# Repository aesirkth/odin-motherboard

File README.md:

# ÆSIR - Odin Motherboard
Odin Motherboard KiCad Design Files

This repository contains the motherboard KiCad design files for the ÆSIR Odin hybrid rocket.
Its main purpose is to house the on-board computer, a Teensy v3.6, and the breakouts to all external components in the rocket. These include: GPS, Go Pro, telemetry, servo, video/camera transmission, accelerometer, umbilical cord, and a safety pin. Use the reference_breakout.txt file to see where each output goes to. 

aesir.lib contains the schematic symbols for the BMP180, MPU-9250, and the motherboard plate (68 mm diameter)

AESIR.pretty contains the footprints for the BMP180, MPU-9250, and the motherboard plate (68 mm diameter).

The Teensy v3.6 KiCad component is required.
Download the schematic symbols and footprints from: 
https://github.com/XenGi/teensy_library

Watch our progress at http://aesir.se/!

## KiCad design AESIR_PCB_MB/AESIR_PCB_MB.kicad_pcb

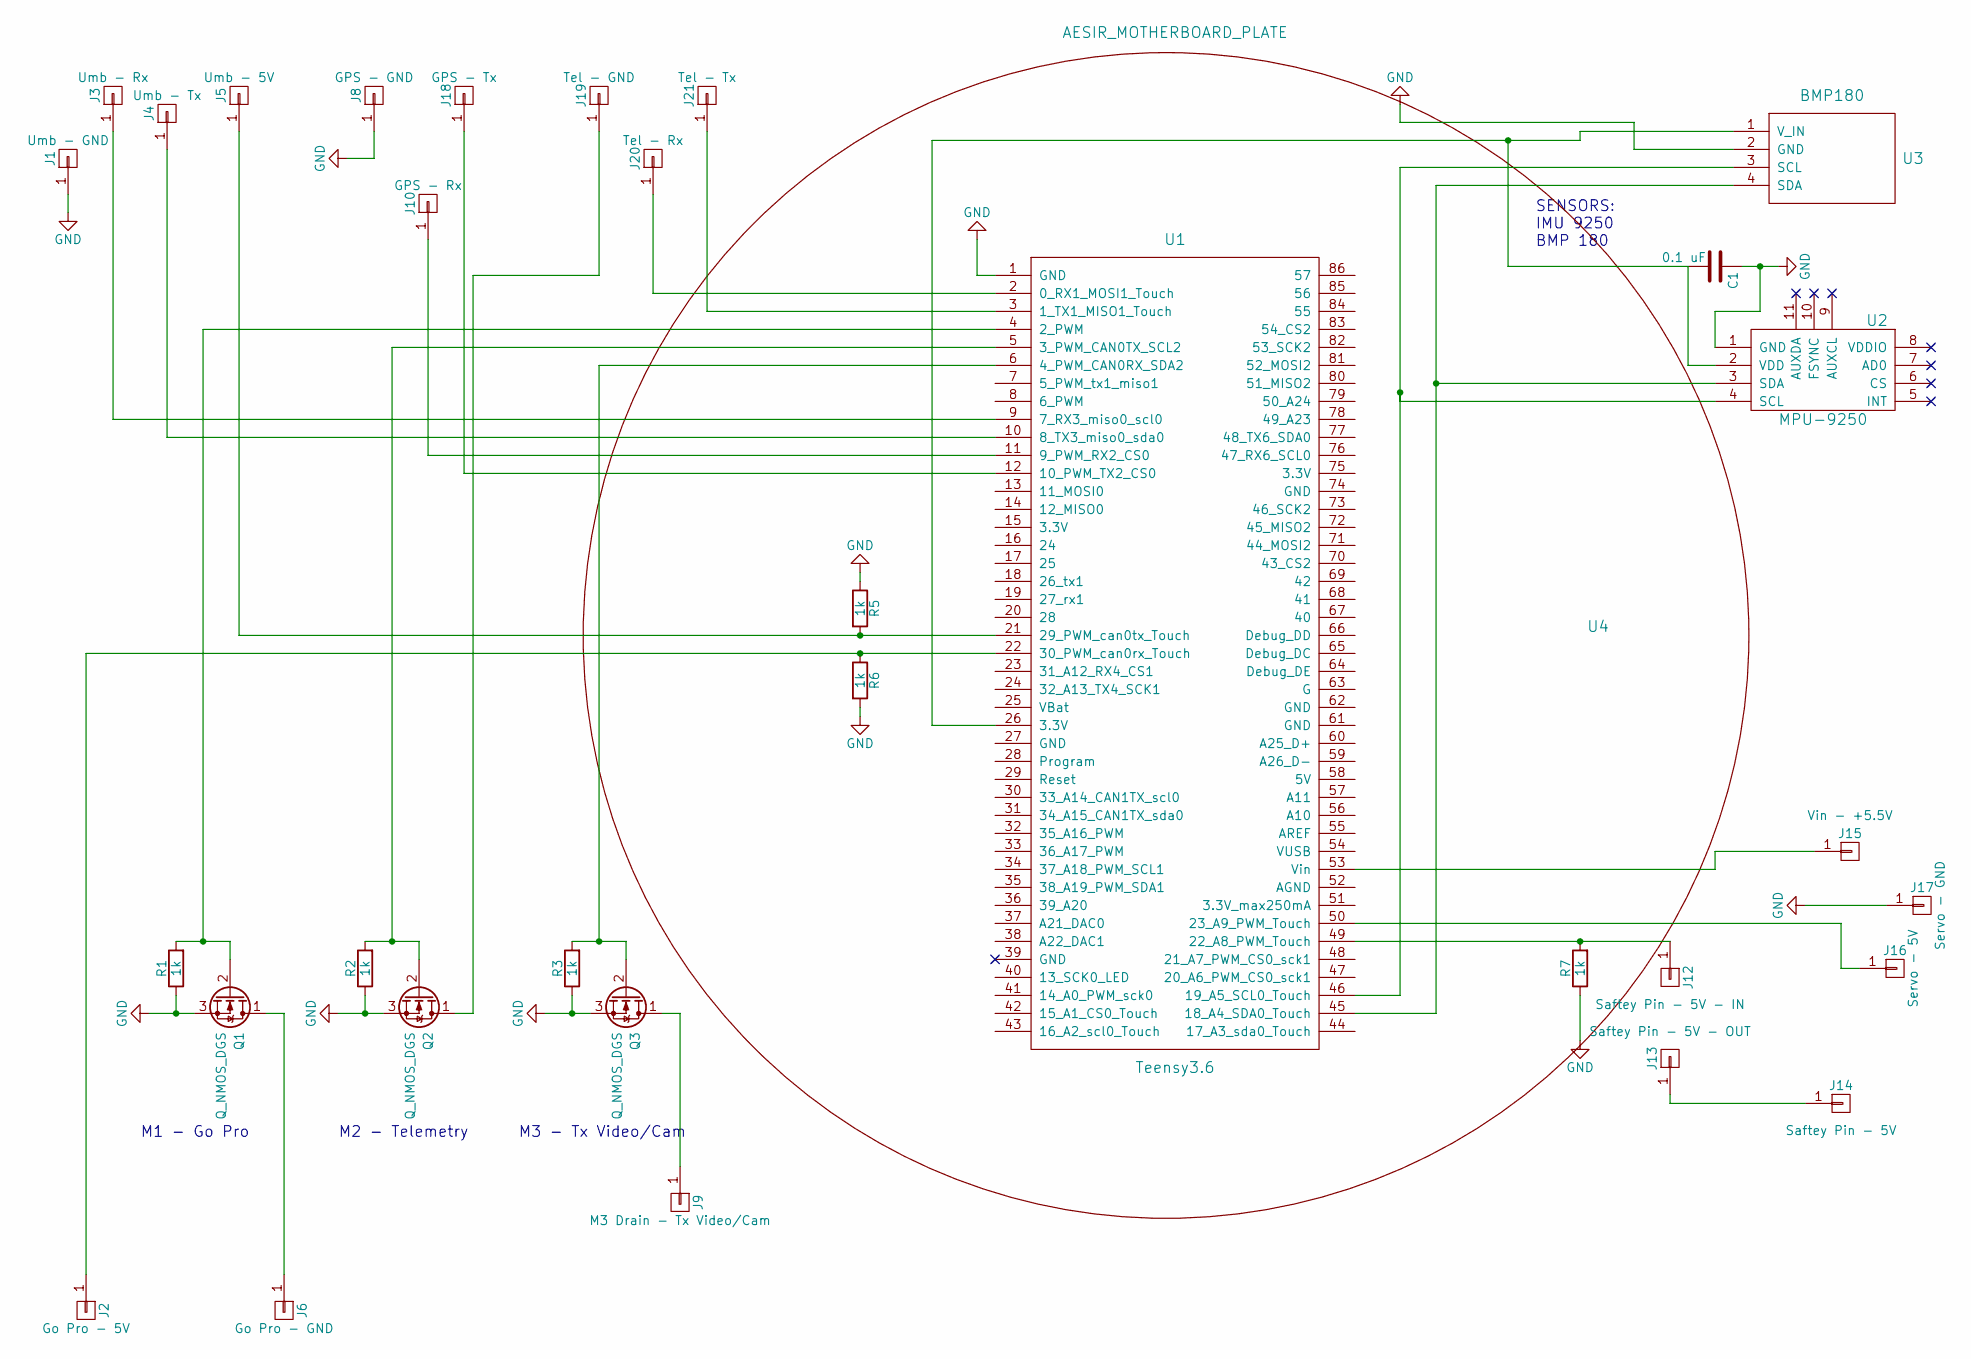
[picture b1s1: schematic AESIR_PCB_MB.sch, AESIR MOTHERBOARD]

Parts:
C1: 0.1 uF; C_0805
J1: Umb - GND; SolderWirePad_single_2mmDrill
J2: Go Pro - 5V; SolderWirePad_single_2mmDrill
J3: Umb - Rx; SolderWirePad_single_2mmDrill
J4: Umb - Tx; SolderWirePad_single_2mmDrill
J5: Umb - 5V; SolderWirePad_single_2mmDrill
J6: Go Pro - GND; SolderWirePad_single_2mmDrill
J8: GPS - GND; SolderWirePad_single_2mmDrill
J9: M3 Drain - Tx Video/Cam; SolderWirePad_single_2mmDrill
J10: GPS - Rx; SolderWirePad_single_2mmDrill
J12: Saftey Pin - 5V - IN; SolderWirePad_single_2mmDrill
J13: Saftey Pin - 5V - OUT; SolderWirePad_single_2mmDrill
J14: Saftey Pin - 5V; SolderWirePad_single_2mmDrill
J15: Vin - +5.5V; SolderWirePad_single_2mmDrill
J16: Servo - 5V; SolderWirePad_single_2mmDrill
J17: Servo - GND; SolderWirePad_single_2mmDrill
J18: GPS - Tx; SolderWirePad_single_2mmDrill
J19: Tel - GND; SolderWirePad_single_2mmDrill
J20: Tel - Rx; SolderWirePad_single_2mmDrill
J21: Tel - Tx; SolderWirePad_single_2mmDrill
Q1, Q2, Q3: Q_NMOS_DGS; SOIC-8-N-AESIR
R1, R2, R3, R5, R6, R7: 1k; R_0805
U1: Teensy3.6; Teensy35_36
U2: MPU-9250
U3: BMP180
U4: AESIR_MOTHERBOARD_PLATE; AESIR_MB_OUTLINE_68mm

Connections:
GND: C1.1, J1.1, J8.1, J17.1, Q1.3 (S), Q2.3 (S), Q3.3 (S), R1.1, R2.1, R3.1, R5.1, R6.2, R7.1, U1.1 (GND), U2.1 (GND), U3.2 (GND)
unnamed: C1.2, U1.26 (3.3V), U2.2 (VDD), U3.1 (V_IN)
unnamed: J2.1, R6.1, U1.22 (30_PWM_can0rx_Touch)
unnamed: J3.1, U1.9 (7_RX3_miso0_scl0)
unnamed: J4.1, U1.10 (8_TX3_miso0_sda0)
unnamed: J5.1, R5.2, U1.21 (29_PWM_can0tx_Touch)
unnamed: J6.1, Q1.1 (D)
unnamed: J9.1, Q3.1 (D)
unnamed: J10.1, U1.11 (9_PWM_RX2_CS0)
unnamed: J12.1, R7.2, U1.49 (22_A8_PWM_Touch)
unnamed: J13.1, J14.1
unnamed: J15.1, U1.53 (Vin)
unnamed: J16.1, U1.50 (23_A9_PWM_Touch)
unnamed: J18.1, U1.12 (10_PWM_TX2_CS0)
unnamed: J19.1, Q2.1 (D)
unnamed: J20.1, U1.2 (0_RX1_MOSI1_Touch)
unnamed: J21.1, U1.3 (1_TX1_MISO1_Touch)
unnamed: Q1.2 (G), R1.2, U1.4 (2_PWM)
unnamed: Q2.2 (G), R2.2, U1.5 (3_PWM_CAN0TX_SCL2)
unnamed: Q3.2 (G), R3.2, U1.6 (4_PWM_CAN0RX_SDA2)
unnamed: U1.45 (18_A4_SDA0_Touch), U2.3 (SDA), U3.4 (SDA)
unnamed: U1.46 (19_A5_SCL0_Touch), U2.4 (SCL), U3.3 (SCL)

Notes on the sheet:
M2 - Telemetry
M1 - Go Pro
SENSORS: IMU 9250 BMP 180
M3 - Tx Video/Cam

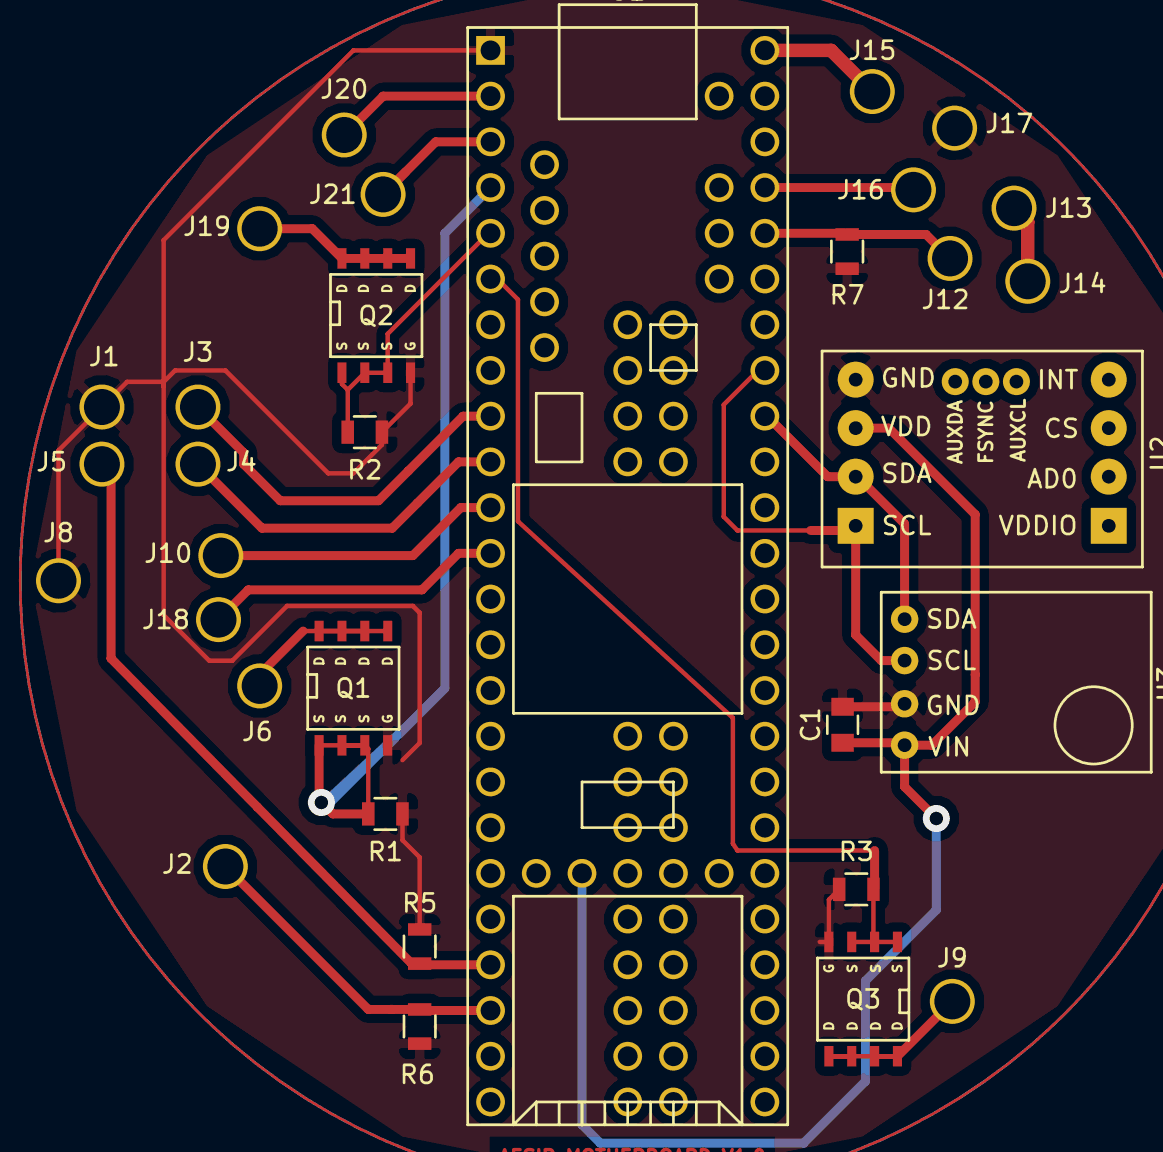
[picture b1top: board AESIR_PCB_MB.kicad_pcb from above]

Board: 2 copper layers, 33 parts (0 on the bottom side), 22 nets.

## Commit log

2017-12-04 added motherboard files
2017-12-04 added breakout references
2017-12-19 finalized motherboard design, added library files
2017-12-19 minor update on board + added more documentation
